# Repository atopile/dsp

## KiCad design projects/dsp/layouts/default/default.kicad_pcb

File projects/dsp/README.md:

# DSP — ato v2

This version preserves the [original DSP v1 circuit and routed layout](https://github.com/atopile/dsp/tree/677818ae8344790a40ca80b10a1c6da4f5feb262/projects/dsp) while
building with the ato v2 runtime from
[monopile PR #4375](https://github.com/atopile/monopile/pull/4375), commit
`c59f4ae02c08cfa813941ea062c983b40992f508`
(`0.16.11.post1.dev843+gc59f4ae02`).

## Build

Open this project with that runtime and library access configured, then run:

```sh
ato build
```

The entry point is `main.ato:DspBoard`. A standalone CLI needs
`ATO_SERVICES_LIBRARY_URL` and a signed-in session or `ATO_SERVICES_LIBRARY_TOKEN`.
No credentials are stored in this project.

## Circuit and layout

`main.ato` connects reusable circuit blocks in `circuits/`: audio channel,
codec, DSP, Ethernet switch, Ethernet ports, host, USB, panel and control.
The block wiring and net names preserve the original board's connectivity.
This includes the input/output coupling capacitors, clamp diodes, reference and
supply decoupling, USB protection, LED resistors and control jumpers omitted from
the earlier simplified fixture. Catalog imports are pinned to `0.1.0`.

The native board preserves the v1 footprint geometry, component positions,
4,994 track segments, 548 vias and 18 copper-fill definitions. Its original
359.01 x 73.78 mm outline has four true rounded corners, ten mounting holes and
the original isolation slot. Import errors in perimeter ordering and a copper
polygon mistakenly classified as a cutout have been corrected.

The board has two combo audio inputs, six XLR audio outputs, two four-channel
analog EtherCON outputs, eight Ethernet ports, DMX input/output, USB-C and a
USBI debug header. See [connector details](CONNECTORS.md).

The CM5 is the real catalog CM5104032. Its carrier footprint incorporates the
two original socket pad banks in place, with their pad numbers translated to
CM5 numbering. Its model aligns to the original four mounting studs. The
combined footprint does not separately procure the two mating sockets.

## Deliberate differences and remaining work

The earlier external-5V power completion is retained in `power.ato`; the
unsolicited three-bank expansion and broad re-placement are reverted. Existing
power ICs retain their original positions, and new support components occupy
the power area. See [power implementation and limits](POWER.md).

The native board contains 424 footprint records: 419 populated/catalog parts
and five board-only features (four test pads and the logo). Compared with v1,
the power section has four more parts and the CM5's three footprint records
(module and two sockets) are represented by one combined carrier footprint.

DRC and physical-check configuration is unchanged. Original routing is retained
for review, not declared manufacturing-ready. The updated power circuit needs
routing reconciliation and its full-channel load exceeds the retained supply
budget. Ethernet magnetics/coupling, USB power behavior, firmware and mechanical
qualification also remain engineering work. Existing check findings are not
hidden by moving the v1 circuitry.

No fallback or migration code is required to build this project. Native
`adopt-board` footprint metadata preserves the intentional v1 pad geometry.

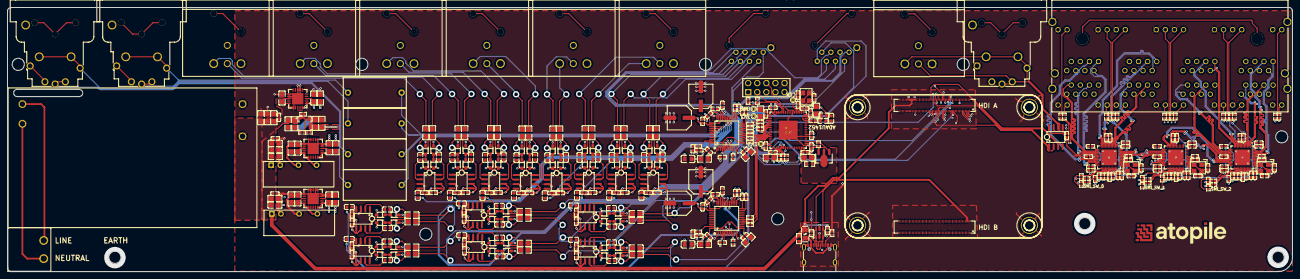
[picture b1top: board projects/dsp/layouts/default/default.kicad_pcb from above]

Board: 4 copper layers, 359.0 x 73.8 mm, 422 parts (0 on the bottom side), 315 nets.

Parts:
C1, C5, C6, C7, C8, C9, C12, C18, C19, C20, C21, C22, C23, C24, C25, C26, C27, C55, C56, C57, C60, C61, C62, C63, C64, C65, C66, C67, C68, C69, C70, C71, C74, C75, C76, C77, C78, C79, C80, C81, C82, C83, C84, C85, C88, C89, C90, C91, C92, C93, C94, C95, C96, C97, C98, C99, C100, C161, C165, C166, C167, C168, C169, C172, C216: 100nF ±10% 16V X7R; C0402
C2, C13, C162, C173: 47µF ±20% 35V; CAP-SMD_BD6.3-L6.6-W6.6-LS7.6-FD
C3, C4, C14, C15, C16, C17, C32, C39, C42, C45, C46, C163, C164: 10µF ±10% 25V X5R; C0805
C10, C170: 5.6nF ±10% 50V X7R; C0402
C11, C171: 390pF ±10% 50V X7R; C0402
C28, C29, C58, C59, C72, C73, C86, C87: 18pF ±5% 50V C0G; C0402
C30: 5.6nF ±10% 50V X7R; C0603
C31: 150pF ±10% 50V X7R; C0603
C33, C34, C40, C41, C43, C44, C47, C48, C49, C50, C51, C52, C53, C54, C101, C102, C108, C109, C115, C116, C122, C123, C129, C130, C136, C137, C143, C144, C150, C151, C174, C175, C181, C182, C188, C189, C195, C196, C202, C203, C209, C210: 22µF ±20% 25V X5R; C0805
C35, C36: 10µF ±10% 25V X7R; C0805
C37, C38: 22µF ±20% 10V X7R; C0805
C103, C106, C107, C110, C113, C114, C117, C120, C121, C124, C127, C128, C131, C134, C135, C138, C141, C142, C145, C148, C149, C152, C155, C156, C176, C179, C180, C183, C186, C187, C190, C193, C194, C197, C200, C201, C204, C207, C208, C211, C214, C215: 10µF ±20% 25V X5R; C0603
C104, C105, C111, C112, C118, C119, C125, C126, C132, C133, C139, C140, C146, C147, C153, C154, C177, C178, C184, C185, C191, C192, C198, C199, C205, C206, C212, C213: 1µF ±10% 25V X5R; C0402
C157, C158, C159, C160: 4.7µF ±5% 100V; CAP-TH_L17.5-W8.5-P15.00-D0.8
CN1, CN2: CONN-SMD_DF40C-100DS-0.4V-51
CN3: CONN-TH_2P-P5.08_DB2ERC-5.08-2P-BK
D1, D2, D4, D5, D6, D7, D8, D9, D10, D11, D12, D13, D14, D15, D16, D17, D18, D19, D20, D21, D22, D23, D24, D25, D26, D27, D28, D29, D30, D31, D32, D33, D34, D35, D36, D37, D38, D39, D40, D41, D42, D43, D44, D45, D46, D47, D48, D49, D50, D51, D52, D53, D54, D55, D56, D57: SOD-323_L1.8-W1.3-LS2.5-RD
D3: SOT-23-6_L2.9-W1.6-P0.95-LS2.8-BL
F1: F0805
J1000, J1001: CONN-TH_NCJ6FA-H
J1002, J1003, J1004, J1005, J1006, J1007: CONN-TH_NC3MAAH
L1, L2: 6.8µH ±20% 550mA 270mΩ; L0805
LOGO1: atopile_Logo_25x6mm
PS1, PS2: RJ45-TH_NE8FAH-C5
PS3: CONN-TH_NC3MAAH
PS4: CONN-TH_NCJ6FA-H
Q1: SOT-89-3_L4.5-W2.5-P1.50-LS4.1-TR
R1, R73: 560Ω ±1% 62.5mW; R0402
R2, R52, R57, R62, R74: 100kΩ ±1% 62.5mW; R0402
R3, R12: 0Ω 100mW; R0603
R4, R15, R16, R27, R51, R53, R54, R56, R58, R59, R61, R63, R64: 10kΩ ±1% 62.5mW; R0402
R5, R6, R7, R8, R9, R10, R23, R24, R25, R26, R45, R46, R47, R48, R49: 0Ω 62.5mW; R0402
R11: 100Ω ±1% 62.5mW; R0402
R13: 4.3kΩ ±1% 100mW; R0603
R14: 1kΩ ±1% 62.5mW; R0402
R17, R18, R19, R20, R21, R22: 1.5kΩ ±1% 62.5mW; R0402
R28, R29, R30, R31, R32, R33, R34, R35, R36, R37, R38, R39, R40, R41, R42, R43: 470Ω ±1% 62.5mW; R0402
R44: 47kΩ ±1% 62.5mW; R0402
R50, R55, R60: 2.49kΩ ±1% 62.5mW; R0402
R65, R66: 5.1kΩ ±1% 62.5mW; R0402
R67, R68, R69, R70, R71, R72, R75, R76, R77: 10Ω ±1% 62.5mW; R0402
R78, R79, R80, R81, R82, R83, R84, R85: 22Ω ±1% 62.5mW; R0402
TP1, TP2, TP3, TP4: TestPoint_THTPad_D1.0mm_Drill0.5mm
U1, U28: LQFP-48_L7.0-W7.0-P0.50-LS9.0-BL
U2: cm5
U3, U4, U5, U6: SMD_BD5.6-D4.1
U7: LFCSP-72_L10.0-W10.0-P0.50-LS10.2-BL-EP5.3
U8: HDR-TH_10P-P2.54-V-M-R2-C5-S2.54-1
U9: RJ45-TH_HC-RJ45-059C-2X4-1
U10, U12, U13: VQFN-20_L5.0-W5.0-P0.65-TL-EP
U11: QFN-7_L4.0-W3.3_TPSM863257RDXR
U14, U15: PWRM-TH_IBXX05S-2WR3
U16: PWRM-TH_L69.5-W39.0_LD30-23B05R2
U17, U18, U19: QFN-48_L6.0-W6.0-P0.40-TL-EP4.4
U20, U21, U22, U23, U24, U25, U26, U27, U29, U30, U31, U32, U33, U34, U35: SOIC-8_L5.0-W4.0-P1.27-LS6.0-BL
USB1: USB-C-SMD_TYPE-C-6PIN-2MD-073
X1: CRYSTAL-SMD_4P-L3.2-W2.5-BL-2
X2, X3, X4: OSC-SMD_4P-L3.2-W2.5-BL_SIT8008BI

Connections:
AL_L: CN3.1, U16.1
CLKOUT: TP1.1, U7.23
CTS: CN1.86, U35.3
EN: R4.2, U11.6
GND: C1.2, C2.2, C3.2, C4.2, C5.2, C6.2, C7.2, C8.2, C9.2, C10.2, C11.2, C12.2, C13.2, C14.2, C15.2, C16.2, C17.2, C18.2, C19.2, C20.2, C21.2, C22.2, C23.2, C24.2, C25.2, C26.2, C27.2, C28.2, C29.2, C32.2, C33.2, C34.2, C35.2, C36.2, C37.2, C38.2, C40.1, C41.1, C42.2, C43.2, C44.2, C46.2, C47.2, C48.2, C49.2, C50.2, C51.2, C52.2, C53.2, C54.2, C55.2, C56.2, C57.2, C58.2, C59.2, C60.2, C61.2, C62.2, C63.2, C64.2, C65.2, C66.2, C67.2, C68.2, C69.2, C70.2, C71.2, C72.2, C73.2, C74.2, C75.2, C76.2, C77.2, C78.2, C79.2, C80.2, C81.2, C82.2, C83.2, C84.2, C85.2, C86.2, C87.2, C88.2, C89.2, C90.2, C91.2, C92.2, C93.2, C94.2, C95.2, C96.2, C97.2, C98.2, C99.2, C100.2, C104.1, C105.2, C111.1, C112.2, C118.1, C119.2, C125.1, C126.2, C132.1, C133.2, C139.1, C140.2, C146.1, C147.2, C153.1, C154.2, C161.2, C162.2, C163.2, C164.2, C165.2, C166.2, C167.2, C168.2, C169.2, C170.2, C171.2, C172.2, C173.2, C177.1, C178.2, C184.1, C185.2, C191.1, C192.2, C198.1, C199.2, C205.1, C206.2, C212.1, C213.2, C216.2, CN1.1, CN1.4, CN1.7, CN1.11, CN1.16, CN1.21, CN1.26, CN1.30, CN1.33, CN1.37, CN1.49, CN1.65, CN1.68, CN1.71, CN1.74, CN1.79, CN1.84, CN1.89, CN1.94, CN1.97, CN1.100, CN2.4, CN2.7, CN2.10, CN2.13, CN2.16, CN2.22, CN2.28, CN2.31, CN2.34, CN2.37, CN2.40, CN2.43, CN2.46, CN2.49, CN2.52, CN2.55, CN2.58, CN2.61, CN2.64, CN2.67, CN2.70, CN2.73, CN2.82, CN2.85, CN2.88, CN2.91, CN2.94, CN2.97, D3.2, PS3.1, PS4.1, PS4.4, R2.2, R27.2, R50.2, R52.2, R55.2, R57.2, R60.2, R62.2, R65.2, R66.2, R74.2, TP2.1, U1.1, U1.4, U1.12, U1.25, U1.32, U1.34, U1.36, U3.1, U3.2, U3.3, U3.4, U3.5, U4.1, U4.2, U4.3, U4.4, U4.5, U5.1, U5.2, U5.3, U5.4, U5.5, U6.1, U6.2, U6.3, U6.4, U6.5, U7.1, U7.6, U7.14, U7.17, U7.19, U7.25, U7.32, U7.33, U7.34, U7.36, U7.37, U7.54, U7.55, U7.72, U7.73, U8.10, U9.9, U9.11, U9.21, U9.23, U9.33, U9.35, U9.45, U9.47, U9.58, U9.60, U9.70, U9.72, U9.82, U9.84, U9.94, U9.96, U9.97, U9.98, U9.99, U9.100, U9.101, U9.102, U10.7, U10.8, U10.11, U10.12, U10.21, U11.4, U12.1, U12.3, U12.20, U13.4, U13.5, U13.6, U13.7, U13.9, U13.10, U13.11, U13.21, U14.2, U15.2, U15.4, U16.4, U17.49, U18.49, U19.49, U20.3, U21.3, U22.3, U23.3, U24.3, U25.3, U26.3, U27.3, U28.1, U28.4, U28.12, U28.25, U28.32, U28.34, U28.36, U29.3, U30.3, U31.3, U32.3, U33.3, U34.3, U35.5, USB1.1, USB1.12, USB1.13, USB1.14, USB1.15, USB1.16, X1.2, X1.4, X2.2, X2.4, X3.2, X3.4, X4.2, X4.4
LED_Gpos0: R36.2, U9.10
LED_Gpos1: R37.2, U9.22
LED_Gpos2: R38.2, U9.34
LED_Gpos3: R39.2, U9.46
LED_Gpos4: R40.2, U9.59
LED_Gpos5: R41.2, U9.71
LED_Gpos6: R42.2, U9.83
LED_Gpos7: R43.2, U9.95
LED_Ypos0: R28.2, U9.12
LED_Ypos1: R29.2, U9.24
LED_Ypos2: R30.2, U9.36
LED_Ypos3: R31.2, U9.48
LED_Ypos4: R32.2, U9.57
LED_Ypos5: R33.2, U9.69
LED_Ypos6: R34.2, U9.81
LED_Ypos7: R35.2, U9.93
PLLFILT: C31.1, R13.1, U7.16
RTS: CN1.25, R2.1, R74.1, U1.10, U28.10
RX: CN1.75, U35.1
TX: CN1.73, U35.4
VDIV_OUTPUT: R27.1, R44.2, U11.7
VDRIVE: Q1.3, R14.2, U7.3
XTALIN_MCLK: R11.1, U7.21
XTALOUT: C29.1, U7.22, X1.3
ad1938s[0]-CM: C1.1, C2.1, U1.38
ad1938s[0]-FILTR: C12.1, C13.1, U1.35
ad1938s[0]-LF: C11.1, R1.1, U1.47
ad1938s[0]-net: C10.1, R1.2
ad1938s[1]-CM: C161.1, C162.1, U28.38
ad1938s[1]-FILTR: C172.1, C173.1, U28.35
ad1938s[1]-LF: C171.1, R73.1, U28.47
ad1938s[1]-net: C170.1, R73.2
adc_channels[0]-analog_left-ADC1LN-0_P: C157.1, U1.40
adc_channels[0]-analog_left-ADC1LP-0_N: C158.1, U1.39
adc_channels[0]-analog_right-ADC1RN-0_P: C159.1, U1.42
adc_channels[0]-analog_right-ADC1RP-0_N: C160.1, U1.41
c1-net: C30.1, R13.2
cc[0]-line: R65.1, USB1.4
cc[1]-line: R66.1, USB1.10
cm5_i2s_resistor_jumpers[2]-logic_out-SD: CN1.88, R7.2
cm5_i2s_resistor_jumpers[5]-logic_out-SD: CN1.87, R10.2
collector: Q1.2, R12.1
crystal-XI-0: C58.1, U17.40, X2.1
crystal-XI-1: C72.1, U18.40, X3.1
crystal-XI-2: C86.1, U19.40, X4.1
crystal-XO-0: C59.1, U17.39, X2.3
crystal-XO-1: C73.1, U18.39, X3.3
crystal-XO-2: C87.1, U19.39, X4.3
dac_channels[0]-analog_left-OL1-0: C103.1, U1.28
dac_channels[0]-analog_left-OL1-1: C145.1, U28.28
dac_channels[0]-analog_right-OR1-0: C110.1, U1.29
dac_channels[0]-analog_right-OR1-1: C152.1, U28.29
dac_channels[1]-analog_left-OL2-0: C117.1, U1.30
dac_channels[1]-analog_left-OL2-1: C176.1, U28.30
dac_channels[1]-analog_right-OR2-0: C124.1, U1.31
dac_channels[1]-analog_right-OR2-1: C183.1, U28.31
dac_channels[2]-analog_left-OL3-0: C131.1, U1.6
dac_channels[2]-analog_left-OL3-1: C190.1, U28.6
dac_channels[2]-analog_right-OR3-0: C138.1, U1.7
dac_channels[2]-analog_right-OR3-1: C197.1, U28.7
dac_channels[3]-analog_left-OL4-1: C204.1, U28.8
dac_channels[3]-analog_right-OR4-1: C211.1, U28.9
dmx_rs485_N: PS3.2, PS4.2, PS4.6, PS4.7, U35.7
dmx_rs485_P: PS3.3, PS4.3, PS4.5, U35.6
ethercon_output_connectors[0]-balanced_audios[0]-audio_out_N: C144.2, PS1.5
ethercon_output_connectors[0]-balanced_audios[0]-audio_out_P: C143.2, PS1.4
ethercon_output_connectors[0]-balanced_audios[1]-audio_out_N: C151.2, PS1.6
ethercon_output_connectors[0]-balanced_audios[1]-audio_out_P: C150.2, PS1.3
ethercon_output_connectors[0]-balanced_audios[2]-audio_out_N: C175.2, PS1.2
ethercon_output_connectors[0]-balanced_audios[2]-audio_out_P: C174.2, PS1.1
ethercon_output_connectors[0]-balanced_audios[3]-audio_out_N: C182.2, PS1.8
ethercon_output_connectors[0]-balanced_audios[3]-audio_out_P: C181.2, PS1.7
ethercon_output_connectors[1]-balanced_audios[0]-audio_out_N: C189.2, PS2.5
ethercon_output_connectors[1]-balanced_audios[0]-audio_out_P: C188.2, PS2.4
ethercon_output_connectors[1]-balanced_audios[1]-audio_out_N: C196.2, PS2.6
ethercon_output_connectors[1]-balanced_audios[1]-audio_out_P: C195.2, PS2.3
ethercon_output_connectors[1]-balanced_audios[2]-audio_out_N: C203.2, PS2.2
ethercon_output_connectors[1]-balanced_audios[2]-audio_out_P: C202.2, PS2.1
ethercon_output_connectors[1]-balanced_audios[3]-audio_out_N: C210.2, PS2.8
ethercon_output_connectors[1]-balanced_audios[3]-audio_out_P: C209.2, PS2.7
footprint-IBREF-0: R50.1, U17.42
footprint-IBREF-1: R55.1, U18.42
footprint-IBREF-2: R60.1, U19.42
i2s_ins[1]-SCK: R77.2, U7.60
i2s_ins[1]-WS: R76.2, U7.61
i2s_outs[1]-SCK: R69.1, U7.43
i2s_outs[1]-WS: R68.1, U7.42
i2s_outs[2]-SCK: R72.1, U7.48
i2s_outs[2]-SD: R70.1, U7.49
i2s_outs[2]-WS: R71.1, U7.47
line_driver_ic-input_signal-VIN-0: C103.2, U20.4
line_driver_ic-input_signal-VIN-1: C190.2, U31.4
line_driver_ic-input_signal-VIN-2: C197.2, U32.4
line_driver_ic-input_signal-VIN-3: C204.2, U33.4
line_driver_ic-input_signal-VIN-4: C211.2, U34.4
line_driver_ic-input_signal-VIN-5: C110.2, U21.4
line_driver_ic-input_signal-VIN-6: C117.2, U22.4
line_driver_ic-input_signal-VIN-7: C124.2, U23.4
line_driver_ic-input_signal-VIN-8: C131.2, U24.4
line_driver_ic-input_signal-VIN-9: C138.2, U25.4
line_driver_ic-input_signal-VIN-10: C145.2, U26.4
line_driver_ic-input_signal-VIN-11: C152.2, U27.4
line_driver_ic-input_signal-VIN-12: C176.2, U29.4
line_driver_ic-input_signal-VIN-13: C183.2, U30.4
line_driver_ic-output_force-anode-0_N: C102.1, C107.2, D6.2, D7.1, U20.1
line_driver_ic-output_force-anode-0_P: C101.1, C106.2, D4.2, D5.1, U20.8
line_driver_ic-output_force-anode-1_N: C189.1, C194.2, D44.2, D45.1, U31.1
line_driver_ic-output_force-anode-1_P: C188.1, C193.2, D42.2, D43.1, U31.8
line_driver_ic-output_force-anode-2_N: C196.1, C201.2, D48.2, D49.1, U32.1
line_driver_ic-output_force-anode-2_P: C195.1, C200.2, D46.2, D47.1, U32.8
line_driver_ic-output_force-anode-3_N: C203.1, C208.2, D52.2, D53.1, U33.1
line_driver_ic-output_force-anode-3_P: C202.1, C207.2, D50.2, D51.1, U33.8
line_driver_ic-output_force-anode-4_N: C210.1, C215.2, D56.2, D57.1, U34.1
line_driver_ic-output_force-anode-4_P: C209.1, C214.2, D54.2, D55.1, U34.8
line_driver_ic-output_force-anode-5_N: C109.1, C114.2, D10.2, D11.1, U21.1
line_driver_ic-output_force-anode-5_P: C108.1, C113.2, D8.2, D9.1, U21.8
line_driver_ic-output_force-anode-6_N: C116.1, C121.2, D14.2, D15.1, U22.1
line_driver_ic-output_force-anode-6_P: C115.1, C120.2, D12.2, D13.1, U22.8
line_driver_ic-output_force-anode-7_N: C123.1, C128.2, D18.2, D19.1, U23.1
line_driver_ic-output_force-anode-7_P: C122.1, C127.2, D16.2, D17.1, U23.8
line_driver_ic-output_force-anode-8_N: C130.1, C135.2, D22.2, D23.1, U24.1
line_driver_ic-output_force-anode-8_P: C129.1, C134.2, D20.2, D21.1, U24.8
line_driver_ic-output_force-anode-9_N: C137.1, C142.2, D26.2, D27.1, U25.1
line_driver_ic-output_force-anode-9_P: C136.1, C141.2, D24.2, D25.1, U25.8
line_driver_ic-output_force-anode-10_N: C144.1, C149.2, D30.2, D31.1, U26.1
line_driver_ic-output_force-anode-10_P: C143.1, C148.2, D28.2, D29.1, U26.8
line_driver_ic-output_force-anode-11_N: C151.1, C156.2, D34.2, D35.1, U27.1
line_driver_ic-output_force-anode-11_P: C150.1, C155.2, D32.2, D33.1, U27.8
line_driver_ic-output_force-anode-12_N: C175.1, C180.2, D36.2, D37.1, U29.1
line_driver_ic-output_force-anode-12_P: C174.1, C179.2, D1.2, D2.1, U29.8
line_driver_ic-output_force-anode-13_N: C182.1, C187.2, D40.2, D41.1, U30.1
line_driver_ic-output_force-anode-13_P: C181.1, C186.2, D38.2, D39.1, U30.8
line_driver_ic-output_sense-SENSEneg-0_N: C107.1, U20.2
line_driver_ic-output_sense-SENSEneg-1_N: C194.1, U31.2
line_driver_ic-output_sense-SENSEneg-2_N: C201.1, U32.2
line_driver_ic-output_sense-SENSEneg-3_N: C208.1, U33.2
line_driver_ic-output_sense-SENSEneg-4_N: C215.1, U34.2
line_driver_ic-output_sense-SENSEneg-5_N: C114.1, U21.2
line_driver_ic-output_sense-SENSEneg-6_N: C121.1, U22.2
line_driver_ic-output_sense-SENSEneg-7_N: C128.1, U23.2
line_driver_ic-output_sense-SENSEneg-8_N: C135.1, U24.2
line_driver_ic-output_sense-SENSEneg-9_N: C142.1, U25.2
line_driver_ic-output_sense-SENSEneg-10_N: C149.1, U26.2
line_driver_ic-output_sense-SENSEneg-11_N: C156.1, U27.2
line_driver_ic-output_sense-SENSEneg-12_N: C180.1, U29.2
line_driver_ic-output_sense-SENSEneg-13_N: C187.1, U30.2
line_driver_ic-output_sense-SENSEpos-0_P: C106.1, U20.7
line_driver_ic-output_sense-SENSEpos-1_P: C193.1, U31.7
line_driver_ic-output_sense-SENSEpos-2_P: C200.1, U32.7
line_driver_ic-output_sense-SENSEpos-3_P: C207.1, U33.7
line_driver_ic-output_sense-SENSEpos-4_P: C214.1, U34.7
line_driver_ic-output_sense-SENSEpos-5_P: C113.1, U21.7
line_driver_ic-output_sense-SENSEpos-6_P: C120.1, U22.7
line_driver_ic-output_sense-SENSEpos-7_P: C127.1, U23.7
line_driver_ic-output_sense-SENSEpos-8_P: C134.1, U24.7
line_driver_ic-output_sense-SENSEpos-9_P: C141.1, U25.7
line_driver_ic-output_sense-SENSEpos-10_P: C148.1, U26.7
line_driver_ic-output_sense-SENSEpos-11_P: C155.1, U27.7
line_driver_ic-output_sense-SENSEpos-12_P: C179.1, U29.7
line_driver_ic-output_sense-SENSEpos-13_P: C186.1, U30.7
logic_out-SCK: CN1.76, R5.2, R8.2
logic_out-WS: CN1.13, R6.2, R9.2
logic_out-pins[23]: CN1.12, R48.2
logic_out-pins[40]: CN1.80, R47.2
model-i2s_ins[0]-SCK-0: R69.2, U1.17
model-i2s_ins[0]-SCK-1: R72.2, U28.17
model-i2s_ins[0]-SCK-2: R5.1, U7.57
model-i2s_ins[0]-SD-0: R67.2, U1.16
model-i2s_ins[0]-SD-1: R70.2, U28.16
model-i2s_ins[0]-SD-2: R7.1, U7.59
model-i2s_ins[0]-WS-0: R68.2, U1.18
model-i2s_ins[0]-WS-1: R71.2, U28.18
model-i2s_ins[0]-WS-2: R6.1, U7.58
model-i2s_ins[1]-SD-2: R75.2, U7.62
model-i2s_outs[0]-SCK-0: R77.1, U1.21
model-i2s_outs[0]-SCK-2: R8.1, U7.40
model-i2s_outs[0]-SD-0: R75.1, U1.20
model-i2s_outs[0]-SD-2: R10.1, U7.41
model-i2s_outs[0]-WS-0: R76.1, U1.22
model-i2s_outs[0]-WS-2: R9.1, U7.39
model-i2s_outs[1]-SD-2: R67.1, U7.44
model-spi-MISO-0: R80.2, U1.24
model-spi-MISO-1: R84.2, U28.24
model-spi-MOSI-0: R79.2, U1.23
model-spi-MOSI-1: R83.2, U28.23
model-spi-SCLK-0: R78.2, U1.26
model-spi-SCLK-1: R82.2, U28.26
model-spi_cs-nCLATCH-0: R81.2, U1.27
model-spi_cs-nCLATCH-1: R85.2, U28.27
nOE: C28.1, R11.2, X1.1
nRE: CN1.27, U35.2
nRESET: CN1.78, U7.24, U8.6
neutral: CN3.2, U16.2
pins[36]: CN1.82, R85.1
pins[47]: CN1.24, R49.2
power_1v8-VCC: CN1.44, CN1.45
power_3v3-VCC: CN1.42, CN1.43
power_3v3_analog: C3.1, C4.1, C5.1, C6.1, C7.1, C8.1, C9.1, C33.1, C34.1, C163.1, C164.1, C165.1, C166.1, C167.1, C168.1, C169.1, L1.1, L1.2, L2.1, L2.2, U1.5, U1.13, U1.33, U1.37, U1.48, U10.1, U10.3, U10.20, U28.5, U28.13, U28.33, U28.37, U28.48
power_3v3_digital: C14.1, C15.1, C17.1, C18.1, C23.1, C24.1, C25.1, C26.1, C27.1, C30.2, C31.2, C37.1, C38.1, C66.1, C67.1, C68.1, C69.1, C70.1, C71.1, C80.1, C81.1, C82.1, C83.1, C84.1, C85.1, C94.1, C95.1, C96.1, C97.1, C98.1, C99.1, C216.1, CN1.39, Q1.1, R14.1, R15.2, R16.2, R17.2, R18.2, R19.2, R20.2, R21.2, R22.2, R44.1, R51.2, R53.2, R54.2, R56.2, R58.2, R59.2, R61.2, R63.2, R64.2, TP3.1, U7.2, U7.7, U7.15, U7.18, U7.38, U7.56, U11.3, U17.6, U17.8, U17.18, U17.31, U17.37, U17.38, U17.48, U18.6, U18.8, U18.18, U18.31, U18.37, U18.38, U18.48, U19.6, U19.8, U19.18, U19.31, U19.37, U19.38, U19.48, U35.8
power_5v: C32.1, C35.1, C36.1, C47.1, C48.1, C49.1, C50.1, C51.1, C52.1, C53.1, C54.1, C55.1, C56.1, C57.1, C100.1, CN1.57, CN1.58, CN1.59, CN1.60, CN1.61, CN1.62, D3.5, F1.2, R3.2, R4.1, U10.13, U10.15, U10.16, U11.1, U14.1, U15.1, U16.3
power_18v_neg: C39.2, C40.2, C41.2, C45.2, C104.2, C111.2, C118.2, C125.2, C132.2, C139.2, C146.2, C153.2, C177.2, C184.2, C191.2, C198.2, C205.2, C212.2, D2.2, D5.2, D7.2, D9.2, D11.2, D13.2, D15.2, D17.2, D19.2, D21.2, D23.2, D25.2, D27.2, D29.2, D31.2, D33.2, D35.2, D37.2, D39.2, D41.2, D43.2, D45.2, D47.2, D49.2, D51.2, D53.2, D55.2, D57.2, U12.4, U12.5, U12.6, U12.7, U12.9, U12.10, U12.11, U12.21, U14.4, U20.5, U21.5, U22.5, U23.5, U24.5, U25.5, U26.5, U27.5, U29.5, U30.5, U31.5, U32.5, U33.5, U34.5
power_18v_pos: C43.1, C44.1, C105.1, C112.1, C119.1, C126.1, C133.1, C140.1, C147.1, C154.1, C178.1, C185.1, C192.1, C199.1, C206.1, C213.1, D1.1, D4.1, D6.1, D8.1, D10.1, D12.1, D14.1, D16.1, D18.1, D20.1, D22.1, D24.1, D26.1, D28.1, D30.1, D32.1, D34.1, D36.1, D38.1, D40.1, D42.1, D44.1, D46.1, D48.1, D50.1, D52.1, D54.1, D56.1, U13.1, U13.3, U13.20, U20.6, U21.6, U22.6, U23.6, U24.6, U25.6, U26.6, U27.6, U29.6, U30.6, U31.6, U32.6, U33.6, U34.6
power_digital-VCC: C16.1, C19.1, C20.1, C21.1, C22.1, R12.2, TP4.1, U7.20, U7.35, U7.53, U7.71
power_vbus-VCC: F1.1, R3.1, USB1.2, USB1.11
regulator_24v_isolated_neg-power_out-VCC: C39.1, C45.1, U12.13, U12.15, U12.16, U14.6
regulator_24v_isolated_pos-power_out-VCC: C42.1, C46.1, U13.13, U13.15, U13.16, U15.6
shield: J1000.8, J1001.8, J1002.4, J1003.4, J1004.4, J1005.4, J1006.4, J1007.4, PS1.9, PS2.9, PS3.4, PS4.8
smi_resistor_jumpers[0]-smi_out-SCL: CN1.28, R17.1, R24.2
smi_resistor_jumpers[0]-smi_out-SDA: CN1.29, R18.1, R23.2
smi_resistor_jumpers[1]-smi_out-SCL: CN1.14, R19.1, R26.2
smi_resistor_jumpers[1]-smi_out-SDA: CN1.85, R20.1, R25.2
smi_resistor_jumpers[2]-smi_out-SCL: CN1.77, R21.1, R46.2
smi_resistor_jumpers[2]-smi_out-SDA: CN1.23, R22.1, R45.2
spi0_cs[0]-pins[38]: CN1.81, R81.1
spi-SCL: CN1.83, R15.1, U7.31, U8.1
spi-SDA: CN1.18, R16.1, U7.30, U8.3
spis[0]-MISO: CN1.20, R80.1, R84.1
spis[0]-MOSI: CN1.22, R79.1, R83.1
spis[0]-SCLK: CN1.19, R78.1, R82.1
switches[0]-_power_1v2-VCC: C60.1, C61.1, C62.1, C63.1, C64.1, C65.1, U17.1, U17.7, U17.13, U17.23, U17.24, U17.35, U17.36, U17.41, U17.43
switches[0]-ethernets[1]-ETH_LED_LINK: R37.1, U17.30
switches[0]-ethernets[1]-ETH_P0_N: U9.14, U17.3
switches[0]-ethernets[1]-ETH_P0_P: U9.13, U17.2
switches[0]-ethernets[1]-ETH_P1_N: U9.18, U17.4
switches[0]-ethernets[1]-ETH_P1_P: U9.15, U17.5
switches[0]-ethernets[2]-ETH_LED_LINK: R41.1, R53.1, U17.32
switches[0]-ethernets[2]-ETH_P0_N: U9.62, U17.11
switches[0]-ethernets[2]-ETH_P0_P: U9.61, U17.12
switches[0]-ethernets[2]-ETH_P1_N: U9.66, U17.10
switches[0]-ethernets[2]-ETH_P1_P: U9.63, U17.9
switches[0]-ethernets[3]-ETH_LED_LINK: R36.1, U17.33
switches[0]-ethernets[3]-ETH_P0_N: U9.2, U17.15
switches[0]-ethernets[3]-ETH_P0_P: U9.1, U17.14
switches[0]-ethernets[3]-ETH_P1_N: U9.6, U17.16
switches[0]-ethernets[3]-ETH_P1_P: U9.3, U17.17
switches[0]-ethernets[4]-ETH_LED_LINK: R40.1, U17.34
switches[0]-ethernets[4]-ETH_P0_N: U9.50, U17.21
switches[0]-ethernets[4]-ETH_P0_P: U9.49, U17.22
switches[0]-ethernets[4]-ETH_P1_N: U9.54, U17.20
switches[0]-ethernets[4]-ETH_P1_P: U9.51, U17.19
switches[0]-i2c_mdio-SCL: R23.1, U17.25
switches[0]-i2c_mdio-SDA: R24.1, U17.26
switches[0]-loop_indication-LDIND_DIS_LD: R51.1, U17.28
switches[0]-reset-RESETB: R47.1, R54.1, U17.27
switches[1]-_power_1v2-VCC: C74.1, C75.1, C76.1, C77.1, C78.1, C79.1, U18.1, U18.7, U18.13, U18.23, U18.24, U18.35, U18.36, U18.41, U18.43
switches[1]-ethernets[0]-ETH_LED_LINK: R43.1, R57.1, U18.29
switches[1]-ethernets[0]-ETH_P0_N: U9.86, U18.45
switches[1]-ethernets[0]-ETH_P0_P: U9.85, U18.44
switches[1]-ethernets[0]-ETH_P1_N: U9.90, U18.46
switches[1]-ethernets[0]-ETH_P1_P: U9.87, U18.47
switches[1]-ethernets[1]-ETH_LED_LINK: R39.1, U18.30
switches[1]-ethernets[1]-ETH_P0_N: U9.38, U18.3
switches[1]-ethernets[1]-ETH_P0_P: U9.37, U18.2
switches[1]-ethernets[1]-ETH_P1_N: U9.42, U18.4
switches[1]-ethernets[1]-ETH_P1_P: U9.39, U18.5
switches[1]-ethernets[2]-ETH_LED_LINK: R42.1, R58.1, U18.32
switches[1]-ethernets[2]-ETH_P0_N: U9.74, U18.11
switches[1]-ethernets[2]-ETH_P0_P: U9.73, U18.12
switches[1]-ethernets[2]-ETH_P1_N: U9.78, U18.10
switches[1]-ethernets[2]-ETH_P1_P: U9.75, U18.9
switches[1]-ethernets[3]-ETH_LED_LINK: R38.1, U18.33
switches[1]-ethernets[3]-ETH_P0_N: U9.26, U18.15
switches[1]-ethernets[3]-ETH_P0_P: U9.25, U18.14
switches[1]-ethernets[3]-ETH_P1_N: U9.30, U18.16
switches[1]-ethernets[3]-ETH_P1_P: U9.27, U18.17
switches[1]-i2c_mdio-SCL: R25.1, U18.25
switches[1]-i2c_mdio-SDA: R26.1, U18.26
switches[1]-loop_indication-LDIND_DIS_LD: R56.1, U18.28
switches[1]-reset-RESETB: R48.1, R59.1, U18.27
switches[2]-_power_1v2-VCC: C88.1, C89.1, C90.1, C91.1, C92.1, C93.1, U19.1, U19.7, U19.13, U19.23, U19.24, U19.35, U19.36, U19.41, U19.43
switches[2]-ethernets[0]-ETH_LED_LINK: R62.1, U19.29
switches[2]-ethernets[2]-ETH_LED_LINK: R63.1, U18.34, U19.32
switches[2]-ethernets[2]-ETH_P0_N: U18.21, U19.11
switches[2]-ethernets[2]-ETH_P0_P: U18.22, U19.12
switches[2]-ethernets[2]-ETH_P1_N: U18.20, U19.10
switches[2]-ethernets[2]-ETH_P1_P: U18.19, U19.9
switches[2]-ethernets[3]-ETH_LED_LINK: R52.1, U17.29, U19.33
switches[2]-ethernets[3]-ETH_P0_N: U17.45, U19.15
switches[2]-ethernets[3]-ETH_P0_P: U17.44, U19.14
switches[2]-ethernets[3]-ETH_P1_N: U17.46, U19.16
switches[2]-ethernets[3]-ETH_P1_P: U17.47, U19.17
switches[2]-ethernets[4]-ETH_LED_LINK: CN1.93, U19.34
switches[2]-ethernets[4]-ETH_P0_N: CN1.5, U19.21
switches[2]-ethernets[4]-ETH_P0_P: CN1.6, U19.22
switches[2]-ethernets[4]-ETH_P1_N: CN1.3, U19.20
switches[2]-ethernets[4]-ETH_P1_P: CN1.2, U19.19
switches[2]-i2c_mdio-SCL: R45.1, U19.25
switches[2]-i2c_mdio-SDA: R46.1, U19.26
switches[2]-loop_indication-LDIND_DIS_LD: R61.1, U19.28
switches[2]-reset-RESETB: R49.1, R64.1, U19.27
usb-USB_D_N: CN2.99, D3.1, D3.6, USB1.5, USB1.7
usb-USB_D_P: CN2.98, D3.3, D3.4, USB1.6, USB1.8
xlr_audio_input_connectors[0]-dmx-GND: J1000.1, J1000.4
xlr_audio_input_connectors[0]-dmx-R_N: C158.2, J1000.3, J1000.5
xlr_audio_input_connectors[0]-dmx-T_P: C157.2, J1000.2, J1000.6, J1000.7
xlr_audio_input_connectors[1]-dmx-GND: J1001.1, J1001.4
xlr_audio_input_connectors[1]-dmx-R_N: C160.2, J1001.3, J1001.5
xlr_audio_input_connectors[1]-dmx-T_P: C159.2, J1001.2, J1001.6, J1001.7
xlr_audio_output_connectors[0]-dmx-audio_out_N: C102.2, J1002.3
xlr_audio_output_connectors[0]-dmx-audio_out_P: C101.2, J1002.2
xlr_audio_output_connectors[1]-dmx-audio_out_N: C109.2, J1003.3
xlr_audio_output_connectors[1]-dmx-audio_out_P: C108.2, J1003.2
xlr_audio_output_connectors[2]-dmx-audio_out_N: C116.2, J1004.3
xlr_audio_output_connectors[2]-dmx-audio_out_P: C115.2, J1004.2
xlr_audio_output_connectors[3]-dmx-audio_out_N: C123.2, J1005.3
xlr_audio_output_connectors[3]-dmx-audio_out_P: C122.2, J1005.2
xlr_audio_output_connectors[4]-dmx-audio_out_N: C130.2, J1006.3
xlr_audio_output_connectors[4]-dmx-audio_out_P: C129.2, J1006.2
xlr_audio_output_connectors[5]-dmx-audio_out_N: C137.2, J1007.3
xlr_audio_output_connectors[5]-dmx-audio_out_P: C136.2, J1007.2

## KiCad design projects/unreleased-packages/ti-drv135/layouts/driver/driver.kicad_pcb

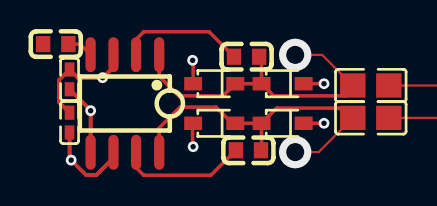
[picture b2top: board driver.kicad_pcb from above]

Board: 2 copper layers, 12 parts (0 on the bottom side), 8 nets.

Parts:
C1, C4: 22µF ±20% 25V X5R; C0805
C2, C5, C6: 10µF ±20% 25V X5R; C0603
C3, C7: 1µF ±10% 25V X5R; C0402
D1, D2, D3, D4: SOD-323_L1.8-W1.3-LS2.5-RD
U1: SOIC-8_L5.0-W4.0-P1.27-LS6.0-BL

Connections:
SENSEneg_N: C6.1, U1.2
SENSEpos_P: C5.1, U1.7
VCC: C7.1, D1.1, D3.1, U1.6
VIN: C2.2, U1.4
anode_N: C4.1, C6.2, D3.2, D4.1, U1.1
anode_P: C1.1, C5.2, D1.2, D2.1, U1.8
negative_power-GND: C3.2, D2.2, D4.2, U1.5
positive_power-GND: C3.1, C7.2, U1.3

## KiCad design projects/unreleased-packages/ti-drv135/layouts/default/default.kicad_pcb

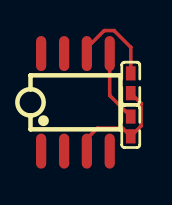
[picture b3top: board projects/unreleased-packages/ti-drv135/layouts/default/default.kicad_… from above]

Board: 2 copper layers, 3 parts (0 on the bottom side), 3 nets.

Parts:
C1, C2: 1µF ±10% 25V X5R; C0402
U1: SOIC-8_L5.0-W4.0-P1.27-LS6.0-BL

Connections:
VCC: C2.1, U1.6
negative_power-GND: C1.2, U1.5
positive_power-GND: C1.1, C2.2, U1.3

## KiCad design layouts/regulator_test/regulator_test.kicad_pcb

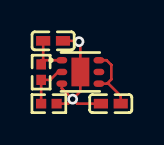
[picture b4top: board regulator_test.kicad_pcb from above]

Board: 2 copper layers, 5 parts (0 on the bottom side), 4 nets.

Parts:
C1, C2: 1µF ±10% 25V X5R; C0402
R1: 2kΩ ±1% 62.5mW; R0402
R2: 10kΩ ±1% 62.5mW; R0402
U1: WSON-6_L2.0-W2.0-P0.65-TL-EP

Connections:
GND: C1.2, C2.2, R1.2, U1.3, U1.7
VDIV_OUTPUT: R1.1, R2.2, U1.2
power_in-VCC: C1.1, U1.4, U1.6
power_out-VCC: C2.1, R2.1, U1.1

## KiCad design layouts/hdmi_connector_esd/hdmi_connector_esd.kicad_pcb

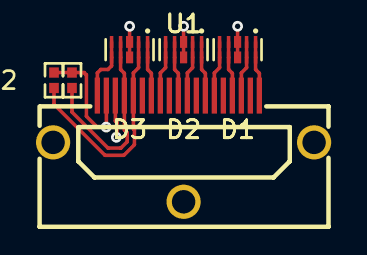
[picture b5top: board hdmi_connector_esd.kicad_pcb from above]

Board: 2 copper layers, 6 parts (0 on the bottom side), 14 nets.

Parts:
D1, D2, D3: DFN2510-10_L2.5-W1.0-P0.50-BL
R1, R2: 10kΩ ±1% 62.5mW; R0402
U1: HDMI-SMD_XDHF-1901-0150

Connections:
CEC: D3.1, D3.10, U1.13
HotPlugDetect: D3.5, D3.6, U1.19
SCL: D3.2, D3.9, R1.1, U1.15
SDA: D3.4, D3.7, R2.1, U1.16
TMDSClockneg: D2.5, D2.6, U1.12
TMDSClockpos: D2.4, D2.7, U1.10
TMDSData0neg: D2.2, D2.9, U1.9
TMDSData0pos: D2.1, D2.10, U1.7
TMDSData1neg: D1.5, D1.6, U1.6
TMDSData1pos: D1.4, D1.7, U1.4
TMDSData2neg: D1.2, D1.9, U1.3
TMDSData2pos: D1.1, D1.10, U1.1
gnd: D1.3, D1.8, D2.3, D2.8, D3.3, D3.8, U1.2, U1.5, U1.8, U1.11, U1.17, U1.20, U1.21, U1.22
hv: R1.2, R2.2, U1.18

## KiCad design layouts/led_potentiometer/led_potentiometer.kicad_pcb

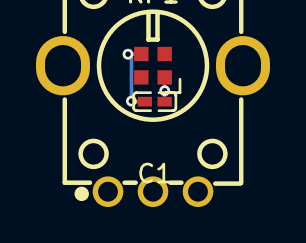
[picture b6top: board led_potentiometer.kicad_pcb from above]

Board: 2 copper layers, 3 parts (0 on the bottom side), 2 nets.

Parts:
C1: 100nF ±10% 16V X7R; C0402
LED1: LED-SMD_4P-L2.0-W2.0-BR
RP1: RES-TH_RK09K1130AAU

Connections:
gnd: C1.2, LED1.3, RP1.4, RP1.5
hv: C1.1, LED1.1

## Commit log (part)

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2025-06-20 top level structure
2025-06-20 added components
2025-06-20 changing the xlr to combination
2025-06-21 adding electrical interfaces to main.ato
2025-06-21 restarting with hardware abstraction
2025-06-21 opamp
2025-06-21 5v rail
2025-06-28 move audio stuff to audio package
2025-06-28 started the main app
2025-07-11 update with latest packages
2025-08-01 add basic modules and components
2025-08-01 add dev docs
2025-09-05 ignore ai configs, start dsp ui project
2025-09-06 digital parts
2025-09-08 checkin layout
2025-09-12 checkin
2025-09-12 tidy up
2025-09-12 remove some local packages
2025-09-13 layout checkin
2025-09-13 ethernet layout
2025-09-13 building with dsp
2025-09-19 organized local packages, imported in ato yaml
2025-09-20 wiggly in place
2025-09-20 layout progress
2025-09-20 almost done with layout
2025-09-20 almost done layout, 90%
2025-09-20 all connections made
2025-09-22 layout ready to generate manufacturing outputs
2025-10-04 fix all f a b r y k _ c o n v e r t errors in parts
2025-10-04 repour after build
2025-10-06 changes complete, ready for review
2025-10-07 cleanup layout and fix pads
2025-10-08 shipped board
2025-11-07 Firmware: Base starting point
2025-11-07 sigma project
2025-11-08 checkin before breaking layout
2025-11-14 Add dmx control project
2025-11-14 add fog machine
2025-11-14 Add other datasheets
2025-11-14 webserver wip
2025-11-14 fix ad1938
2025-11-14 fix selfhost
2025-11-14 enable spi in config
2025-11-15 setup volume control
2025-11-17 new fw
2026-01-23 publish ti drv-135 and xlr-connector packages, upgrade dependencies to latest in yaml
